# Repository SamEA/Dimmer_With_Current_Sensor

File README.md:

Dimmer
======

A simple Dimmer for Halogen/Incandescent lamp

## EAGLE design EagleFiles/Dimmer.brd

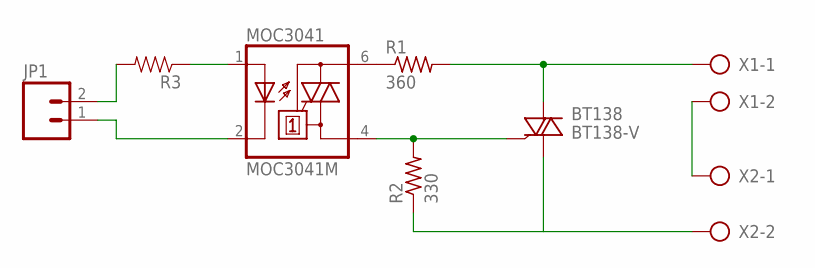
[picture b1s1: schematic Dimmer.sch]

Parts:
BT138: BT138-V; TO220BV
JP1: M02PTH; 1X02
MOC3041: MOC3041M; DIL06
R1: 360; 0309V
R2: 330; 0309V
R3: RESISTOR0603-RES; 0603-RES
X1, X2: AK500/2

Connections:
unnamed: MOC3041.6 (A2), R1.1
unnamed: X1.2, X2.1
unnamed: BT138.G, MOC3041.4 (A1), R2.2
unnamed: BT138.T1 (A1), R2.1, X2.2
unnamed: BT138.T2 (A2), R1.2, X1.1
unnamed: MOC3041.1 (A), R3.1
unnamed: JP1.1, MOC3041.2 (C)
unnamed: JP1.2, R3.2

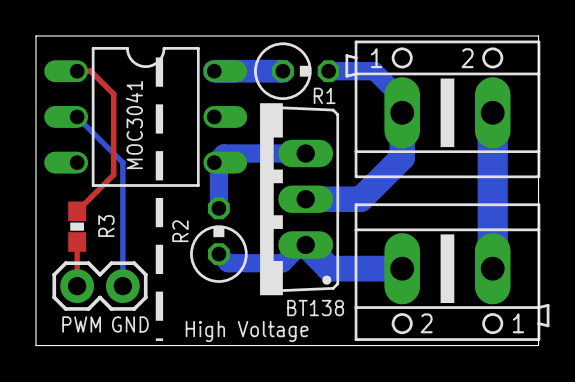
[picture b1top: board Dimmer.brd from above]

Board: 2 copper layers, 27.9 x 17.2 mm, 8 parts (0 on the bottom side), 8 nets.

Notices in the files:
parts and their libraries:
SparkFun-Passives: Licensing: CC v3.0 Share-Alike You are welcome to use this library for commercial purposes.
